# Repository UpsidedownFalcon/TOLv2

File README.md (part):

# TOLv2: Wearable IMU Logger for Synchronised Multi-Person Motion Capture 

## Contents

- [Introduction](#introduction)
- [Rationale](#rationale)
- [System overview](#system-overview)
  - [Level 1: system context](#level-1-system-context)
  - [Level 2: modules](#level-2-modules)
- [System breakdown](#system-breakdown)
  - [USBC: connector and protection](#usbc-connector-and-protection)
  - [BMS: charger, fuel gauge and cell](#bms-charger-fuel-gauge-and-cell)
  - [SNS: sensors and main rail](#sns-sensors-and-main-rail)
  - [MCU: SoC, clocks and radio](#mcu-soc-clocks-and-radio)
  - [SD: card and card rail](#sd-card-and-card-rail)
  - [UI: button, LED and debug](#ui-button-led-and-debug)
  - [PCB](#pcb)
- [JLCPCB ordering](#jlcpcb-ordering)
- [Firmware rules](#firmware-rules)
  - [F1: charger](#f1-charger)
  - [F2: storage](#f2-storage)
  - [F3: sensors](#f3-sensors)
  - [F4: clock](#f4-clock)
  - [F5: card](#f5-card)
  - [F6: GPIO and buses](#f6-gpio-and-buses)
  - [F7: timing and sleep](#f7-timing-and-sleep)
  - [F8: recovery](#f8-recovery)
  - [Rails](#rails)
  - [IMU](#imu)

## Introduction

TOL v2 is an open-hardware inertial logger that a person wears. The logger records acceleration, angular rate and magnetic field. A maximum of 32 devices record on one time reference.

- **Size:** 35.4 mm × 21.4 mm × 9.9 mm with battery and enclosure.
- **IMU (inertial measurement unit):** 6-axis ICM-45686, anti-aliased output, 6.4 kHz maximum.
- **Magnetometer:** 3-axis MMC5983MA, output 1 kHz maximum.
- **Cell:** 150 mAh LiPo. Approximately 9 days of continuous record at 100 Hz (0.64 mA).
- **Standby:** approximately 6 months at 32 µA, with wake on motion.
- **Card:** removable microSD card, 8 GB minimum.
- **USB-C:** cell charge and full-speed data transfer (12 Mbit/s).
- **Radio:** Bluetooth Low Energy (BLE) with a long-range mode and a 2 Mbit/s mode.
- **Sync:** BLE beacons give the time reference. The target error between devices is 1 ms.
- **Clock:** one temperature-compensated crystal oscillator (TCXO) for the system on chip (SoC) and the IMU. Hardware timestamps for events.
- **Charge control:** programmable charger and fuel gauge.

## Rationale

TOL v2 is designed as a successor to the Tiny Open Logger (TOL v1): 

| Gap in earlier work | Source | TOL v2 response |
|---|---|---|
| A timestamp is a sample count multiplied by a nominal interval. | TOL v1 | The interrupt lines of the sensors connect to a capture timer. A TCXO is the clock source of the real-time counter. |
| The clock rates of 2 devices are different by 40 to 67 ppm. The offset is 336 ms maximum after 2 h. | TOL v1 | Each device has a TCXO with a tolerance of ±1.9 ppm at 0 to 50 °C. |
| There is no sync between devices. Sync with magnet pulses has an error of 7 to 40 ms and a range of 11 cm. | TOL v1 | BLE beacons give one time reference to all devices. The target error is 1 ms. |
| A device that streams data has sync. But this device uses 350 mA and needs Wi-Fi and a server. | HARNode (Lepold et al., 2025) | Each device records to its card. The current calculation has the receiver on for 2 ms each second. |
| The download uses flash memory at 1 MHz, CSV text and one Wi-Fi access point for each device. | TOL v1 | The card is removable. USB transfers the files at full speed. USB hubs connect a group of devices to one host PC. |
| There is no sleep mode, no fuel gauge and no measured current. The SoC uses 17 to 28 mA. | TOL v1 | Calculated current: 0.58 mA in normal record mode, 32 µA in standby. The board has a fuel gauge and a programmable charger. |
| Rules for home-made boards limit the design. Manual assembly of LGA parts is not a task for a non-expert. | TOL v1 | An assembly service makes the board. All fitted parts are in the JLCPCB parts library. |
| The button shares a boot pin of the SoC. | TOL v1 | The button connects to a GPIO pin with no boot function. |
| Sessions have 6 to 20 persons and last approximately 2 h. Download was one device at a time. Children touch the devices. Sweat goes into the devices. | Ward et al., 2018; Sun et al., 2026 | A maximum of 32 devices. Charge and download through USB hubs. One button, for use below a membrane. |

## System overview

### System context

```mermaid
flowchart LR
    wearer("Wearer")
    researcher("Researcher")
    beacon["Beacon source<br/>BLE time reference"]
    host["Host PC and USB hubs<br/>5 V supply, file download"]
    probe["Debug probe<br/>SWD"]
    tol["TOL v2 device<br/>records motion with hardware timestamps"]

    wearer -->|"motion, magnetic field"| tol
    researcher -->|"button"| tol
    tol -->|"LED: identity, state, charge"| researcher
    beacon -->|"BLE beacons"| tol
    host ==>|"USB-C: 5 V"| tol
    tol -->|"USB: files"| host
    probe -->|"program, debug"| tol
```

- The researcher starts and stops a session with the button.
- The LED shows the device identity, the device state and the state of charge.
- The beacon source sends a BLE beacon at intervals of 60 s maximum. This repository does not contain a beacon source.

### Modules

```mermaid
flowchart TB
    subgraph board["TOL v2 device"]
        direction TB
        USBC["USBC<br/>J1 receptacle, D1 ESD"]
        BMS["BMS<br/>U2 charger, U3 fuel gauge, BT1 cell"]
        SNS["SNS<br/>U7 regulator, U5 IMU, U6 magnetometer"]
        MCU["MCU<br/>U1 SoC, Y1 TCXO, X1 crystal, ANT1"]
        SD["SD<br/>U4 regulator, J2 microSD socket"]
        UI["UI<br/>SW1 button, D2 LED, J3 debug pads"]
    end

    USBC ==>|"VBUS"| BMS
    USBC ==>|"VBUS"| MCU
    BMS ==>|"SYS"| SNS
    BMS ==>|"SYS"| SD
    BMS ==>|"SYS"| UI
    SNS ==>|"VDD 3.0 V"| MCU
    SNS ==>|"VDD 3.0 V"| UI

    USBC ---|"USB, 12 Mbit/s"| MCU
    SNS ---|"SPIM2 4 MHz<br/>TWIM1 100 kHz<br/>IMU_INT, MAG_INT<br/>CLK32K_IMU 32.768 kHz"| MCU
    MCU ---|"SPIM3 16 MHz<br/>SD_EN, SD_DET"| SD
    BMS ---|"TWIM0 100 kHz<br/>CHG_INT, FG_ALRT"| MCU
    MCU ---|"LED_DIN, BTN, SWD"| UI
    MCU -.-> SNS
```

External connections: host PC to USBC, beacon source to MCU, wearer to SNS, researcher and debug probe to UI.

| Module | Input | Process | Output |
|---|---|---|---|
| USBC (USB-C connector) | 5 V and USB data from the cable; electrostatic discharge | Identifies the device as a power sink. Clamps electrostatic discharges. | `VBUS`; USB data pair |
| BMS (battery management) | `VBUS`; settings on TWIM0 | Selects the power source. Charges the cell. Measures the state of charge. | `SYS`; `CHG_INT`; `FG_ALRT`; state-of-charge data on TWIM0 |
| SNS (sensors) | `SYS`; motion; magnetic field; `CLK32K_IMU`; commands on SPIM2 and TWIM1 | Regulates `SYS` to 3.0 V. Measures acceleration, angular rate and magnetic field. | `VDD`; samples on SPIM2 and TWIM1; `IMU_INT`; `MAG_INT` |
| MCU (microcontroller) | `VDD`; `VBUS`; samples; `IMU_INT`; `MAG_INT`; `BTN`; `SD_DET`; `CHG_INT`; `FG_ALRT`; state-of-charge data; beacons; USB data | Gives timestamps to events. Holds samples in a buffer. Writes files. Operates BLE and USB. | Card data on SPIM3; `SD_EN`; `LED_DIN`; `CLK32K_IMU`; commands on SPIM2 and TWIM1; settings on TWIM0; BLE packets; USB data |
| SD (card) | `SYS`; `SD_EN`; card data on SPIM3 | Switches the card rail. Stores files. | `SD_DET`; card data on SPIM3 |
| UI (user interface) | `SYS`; `VDD`; button press; `LED_DIN`; SWD signals from the debug probe | Sets `BTN` high during a press. Shows the device state. Connects the debug probe to the SoC. | `BTN`; light; SWD signals to the SoC |

**Power**

```mermaid
flowchart LR
    J1["J1 USB-C"] ==>|"VBUS 5 V"| U2["U2 charger<br/>power path"]
    BT1["BT1 cell<br/>150 mAh"] ==>|"BAT"| U2
    BT1 ---|"BAT"| U3["U3 fuel gauge"]
    U2 ==>|"SYS"| U7["U7 regulator<br/>always on"]
    U2 ==>|"SYS"| U4["U4 regulator<br/>switched by SD_EN"]
    U2 ==>|"SYS"| D2["D2 LED"]
    U7 ==>|"VDD 3.0 V"| loads["U1 SoC, U5 IMU,<br/>U6 magnetometer, Y1 TCXO"]
    U4 ==>|"3V0_SD 3.0 V"| J2["J2 microSD socket"]
    J1 ==>|"VBUS through R5"| usb["U1 USB supply pin"]
```

- U2 supplies `SYS` from `VBUS` when `VBUS` is present. If not, U2 supplies `SYS` from the cell.
- U7 supplies the main rail `VDD` (3.0 V) at all times.
- U4 supplies the card rail `3V0_SD` (3.0 V) only while `SD_EN` is high.

**Data**

- The IMU and the card each have an SPI master. A card write does not stop a sensor read.
- The charger and the fuel gauge share one I2C bus. The magnetometer has a second I2C bus.

**Timing**

```mermaid
flowchart LR
    Y1["Y1 TCXO<br/>32.768 kHz"] -.->|"R1"| RTC["RTC<br/>30.5 µs periods"]
    Y1 -.->|"R2"| U5["U5 IMU<br/>sample clock"]
    X1["X1 crystal<br/>32 MHz"] -.-> TIMER["Capture timer<br/>62.5 ns ticks"]
    RTC -->|"event: start"| TIMER
    U5 -->|"IMU_INT: capture"| TIMER
    U6["U6 magnetometer"] -->|"MAG_INT: capture"| TIMER
    RADIO["RADIO<br/>beacon address"] -->|"capture"| TIMER
    RTC --> TS["Timestamp =<br/>RTC count + timer ticks"]
    TIMER --> TS
```

- Y1 is the clock source of the real-time counter (RTC) of the SoC and of the IMU.
- An RTC event starts the capture timer. A sensor edge or a beacon captures the timer value.
- The capture timer operates only in a capture interval. The current calculation uses one interval of 2 ms each second.
- Each device calculates its offset and rate from the beacons.

**Modes**

| Mode | Calculated current | Wake source |
|---|---|---|
| Normal record mode | 0.58 mA | |
| Standby | 32 µA | Motion |
| Off | 15.1 µA | Button |
| Device storage | 3.5 µA | |

- Normal record mode: IMU setting 100 Hz, magnetometer 25 Hz.
- High-rate record mode: IMU setting 400 Hz, magnetometer 100 Hz.
- Records use 16-bit samples.
- In off mode the SoC is in System OFF. A button press starts the SoC.

## System breakdown
### USBC: connector and protection

Sheet: [electronics/USBC.kicad_sch](electronics/USBC.kicad_sch)

| Part | Input | Process | Output |
|---|---|---|---|
| J1 USB-C receptacle, R3, R4 | 5 V and USB data from a USB host or charger | Connects the cable to the board. R3 and R4 (5.1 kΩ) identify the device as a power sink. | `VBUS` (5 V); `USB_D+`; `USB_D-` |
| D1 ESD array (AOZ8904CIL) | Electrostatic discharge on `USB_D+`, `USB_D-` or `VBUS` | Clamps the line voltage. | Clamped voltage on the line |

- USB 2.0 only. The CC lines connect only to R3 and R4. The device can use default USB power only.
- The USB data pair connects directly to the SoC. The speed is 12 Mbit/s (full speed).
- The working voltage of D1 is 5.5 V. D1 does not protect the USB supply pin of the SoC.
- The capacitance on `VBUS` is 9.4 µF nominal and 10.3 µF at +10 % tolerance. The USB-C limit for a sink is 10 µF.

### BMS: charger, fuel gauge and cell

Sheet: [electronics/BMS.kicad_sch](electronics/BMS.kicad_sch)

| Part | Input | Process | Output |
|---|---|---|---|
| U2 charger (BQ25180, I2C address 0x6A) | `VBUS`; `BAT`; temperature signal from RT1; settings on TWIM0 | Supplies `SYS` from `VBUS` or from the cell. Charges the cell at the set current and voltage. | `SYS`; charge current; `CHG_INT` |
| U3 fuel gauge (MAX17048, I2C address 0x36) | Cell voltage on `BAT` | Calculates the state of charge. | State-of-charge data on TWIM0; `FG_ALRT` |
| RT1 thermistor (10 kΩ NTC) | Board temperature near U2 | Changes its resistance with temperature. | Temperature signal to U2 |
| BT1 pads for the cell pack | Charge current from U2 | The cell pack stores the energy. | `BAT` |

- A cell pack is a 150 mAh LiPo cell with a protection circuit. The assembler does not fit the cell pack.
- Firmware writes the charge settings for this cell. See [F1](#f1-charger).
- Only the fuel gauge measures the cell voltage. See [Rails](#rails).
- The board has no protection circuit and no reverse-polarity protection.
- Pad 1 of BT1 is positive. Examine the polarity before you solder the cell pack.
- Cell limits: charge at 150 mA maximum, at 0 to 45 °C. Discharge at 300 mA maximum.

### SNS: sensors and main rail

Sheet: [electronics/SNS.kicad_sch](electronics/SNS.kicad_sch)

| Part | Input | Process | Output |
|---|---|---|---|
| U7 regulator (TPS7A0230) | `SYS` | Regulates `SYS` to 3.0 V at all times. | `VDD` for the SoC, the sensors, the TCXO and the pull-up resistors |
| U5 IMU (ICM-45686) | `VDD`; motion; `CLK32K_IMU`; commands on SPIM2 | Measures acceleration and angular rate on 3 axes each. Holds 8 kB maximum in its buffer. | Samples on SPIM2; `IMU_INT` (data ready or buffer level) |
| U6 magnetometer (MMC5983MA, I2C address 0x30) | `VDD`; magnetic field; commands on TWIM1 | Measures the field on 3 axes with 18 bits. | Samples on TWIM1; `MAG_INT` (measurement complete) |

- The enable pin of U7 connects to `SYS`. Firmware cannot set `VDD` to off. The sensors sleep by command ([F3](#f3-sensors)).
- With the clock from Y1, the IMU rate is the set rate × 1.024. A setting of 100 Hz gives 102.4 Hz.
- TDK application note AN-000478 gives this ratio for low-noise mode. The design uses the same ratio for low-power mode.
- `VDD` stays at 3.0 V until `SYS` decreases to approximately 3.3 V. Below this voltage, `VDD` decreases with `SYS`.
- Minimum supply voltage: magnetometer 2.8 V, IMU 1.71 V, SoC 1.7 V.
- U7 is stable with 0.5 to 22 µF. `VDD` has 13.1 to 20.8 µF effective (calculated).

### MCU: SoC, clocks and radio

Sheet: [electronics/MCU.kicad_sch](electronics/MCU.kicad_sch)

| Part | Input | Process | Output |
|---|---|---|---|
| U1 SoC (nRF52840) | `VDD`; `VBUS` through R5; `CLK32_MCU`; samples; `IMU_INT`; `MAG_INT`; `BTN`; beacons; USB data | Gives timestamps to events. Holds samples in a buffer. Writes files to the card. Operates BLE and USB. | Card data on SPIM3; `SD_EN`; `LED_DIN`; sensor commands; charger settings; BLE packets; USB data |
| Y1 TCXO (TG-3541CE), R24, C47 | `VDD` through the filter R24 and C47 | Makes a 32.768 kHz clock with temperature compensation. | `CLK32_MCU` through R1; `CLK32K_IMU` through R2 |
| X1 crystal (32 MHz), C1, C2 | Drive from U1 | Sets the frequency of the high-frequency clock. | Clock for the radio, USB and the capture timer |
| ANT1 chip antenna, C3, L1, C4, L5, L6 | 2.4 GHz signal from U1; radio waves | Connects U1 to the antenna through the matching network. Transmits and receives. | Radio waves; 2.4 GHz signal to U1 |

SoC pin map. High is `VDD` (3.0 V). Low is ground. TWIM, SPIM and I2S are peripherals of the nRF52840.

| Pin | Net | Direction | Function | Notes |
|---|---|---|---|---|
| `P0.00` | `CLK32_MCU` | In | XL1 | 32.768 kHz from Y1 through R1 |
| `P0.04` | `BTN` | In | GPIO, wake | High = press. Internal pull-down |
| `P0.05` | `MAG_INT` | In | Timer capture | High = measurement complete |
| `P0.06` | `IMU_MISO` | In | SPIM2 MISO | |
| `P0.07` | `IMU_INT` | In | Timer capture | Data ready or buffer level |
| `P0.08` | `IMU_CS` | Out | GPIO | Low = IMU selected |
| `P0.11` | `BMS_SCL` | Out | TWIM0 SCL | R6, 10 kΩ to `VDD` |
| `P0.12` | `BMS_SDA` | In/out | TWIM0 SDA | R7, 10 kΩ to `VDD` |
| `P0.13` | `LED_DIN` | Out | I2S data out | R22 pull-down. Idle low |
| `P0.14` | `SD_EN` | Out | GPIO | High = card rail on. R20 pull-down |
| `P0.15` | `CHG_INT` | In | GPIO | Low pulse = charger event. Internal pull-up |
| `P0.16` | `SD_DET` | In | GPIO | Low = no card. Internal pull-up only during a read |
| `P0.17` | `SD_CS` | Out | SPIM3 CSN | Low = card selected |
| `P0.18` | `NRESET` | In | Reset | From J3. Only after UICR PSELRESET = 18 |
| `P0.19` | `SD_SCK` | Out | SPIM3 SCK | R21 pull-down |
| `P0.20` | `MAG_SCL` | Out | TWIM1 SCL | R9, 10 kΩ to `VDD` |
| `P0.21` | `SD_MOSI` | Out | SPIM3 MOSI | To the card CMD pin |
| `P0.22` | `MAG_SDA` | In/out | TWIM1 SDA | R19, 10 kΩ to `VDD` |
| `P0.23` | `SD_MISO` | In | SPIM3 MISO | From the card DAT0 pin |
| `P0.25` | `FG_ALRT` | In | GPIO | Low = alert. Internal pull-up |
| `P0.26` | `IMU_SCK` | Out | SPIM2 SCK | |
| `P0.27` | `IMU_MOSI` | Out | SPIM2 MOSI | |
| `P1.00` | `SWO` | Out | Trace | To J3. Optional |

- GPIO pins that are not in the table have no connection. The I2S block uses `P0.24` and `P1.08` as clock outputs ([F6](#f6-gpio-and-buses)).
- The SoC operates in normal voltage mode. Its 2 supply inputs connect to `VDD`. See [Rails](#rails).
- Y1 tolerance: ±1.9 ppm at 0 to 50 °C. Y1 gives a valid clock 3 s maximum after power-on.
- Y1 needs its supply at 0 V for more than 10 s before a new power-on.
- With no beacon for 10 min, the time difference between 2 devices increases to 2.3 ms maximum (calculated).
- The 2.3 ms figure includes only the ±1.9 ppm tolerance of Y1. With solder shift, ageing and supply tolerance, the figure is 10.7 ms.
- The target timestamp error is 5 µs.
- C44 and C45 are not fitted. They are positions for antenna tuning parts. The matching network is not tuned for this board.
- TP4 is a bare test pad on the output of Y1.
- C9 (820 pF) is necessary for this SoC variant, NRF52840-QIAA-R.
- The debug port is not locked on this SoC variant.

### SD: card and card rail

Sheet: [electronics/SD.kicad_sch](electronics/SD.kicad_sch)

| Part | Input | Process | Output |
|---|---|---|---|
| U4 regulator (TPS7A0230) | `SYS`; `SD_EN` | Supplies 3.0 V while `SD_EN` is high. Discharges the card rail when off. | `3V0_SD` |
| J2 microSD socket (TF-110) and card | `3V0_SD`; card data on SPIM3 | Operates in SPI mode. Stores the files. | Card data on SPIM3; `SD_DET` (low = no card) |
| R12 to R16, R20, R21 | SoC pins that float during a reset | R12 to R16 pull the card lines up to `3V0_SD`. R20 holds `SD_EN` low. R21 holds `SD_SCK` low. | Defined levels on the card lines |

- The assembler does not fit a card.
- Data rate: 1.9 kB/s (21 MB in 3 h) in normal record mode, 7.8 kB/s (84 MB in 3 h) in high-rate record mode.
- The card rail is on only during a buffer write: approximately each 67 s in normal record mode.
- R12 to R16 connect to `3V0_SD`. As a result, the resistors cannot supply a card that has no power.

### UI: button, LED and debug

Sheet: [electronics/UI.kicad_sch](electronics/UI.kicad_sch)

| Part | Input | Process | Output |
|---|---|---|---|
| SW1 button | A press; `VDD` | Connects `VDD` to `BTN` during a press. | `BTN` (high = press) |
| D2 RGB LED (WS2812B) | `SYS`; `LED_DIN` at 800 kbit/s | Decodes the colour data. | Light: device identity, device state, state of charge |
| J3 debug pads (Tag-Connect TC2030) | SWD signals from the debug probe | Connects the debug probe to the SoC. | `SWDIO`; `SWCLK`; `NRESET`; `SWO` |

- J3 has 6 bare pads: `VDD`, `SWDIO`, `NRESET`, `SWCLK`, GND, `SWO`.
- TP1, TP2, TP3 and TP5 are bare test pads: `BAT`, `SYS`, `VDD`, GND.
- `SYS` supplies the LED. The LED data level comes from `VDD`. This level limits `SYS` to 4.4 V. See [F1](#f1-charger).
- The sensor interrupt lines have no test pads.

### PCB

Board: [electronics/TOLv2.kicad_pcb](electronics/TOLv2.kicad_pcb). Custom rules: [electronics/TOLv2.kicad_dru](electronics/TOLv2.kicad_dru).

- Size: 26.5 mm × 17.78 mm. Copper layers: 6. Finish: ENIG.
- Stack-up: JLC06081H-2116. Thickness: 0.83 mm ± 0.10 mm.
- Footprints: 81. 70 are on the top side and 11 are on the bottom side. The assembler fits 72.
- Not fitted: BT1, J3, TP1 to TP5, C44, C45.
- Vias: 178 through vias, all filled and capped. 99 are in a pad. 124 have a 0.15 mm hole.
- Minimum track and gap: 0.10 mm.
- Target impedance (calculated): 50 Ω for the antenna feed, 90 Ω for the USB data pair.
- KiCad 10.0.8 checks: DRC gives 0 violations. ERC gives 0 errors and 3 label warnings.

| Layer | Use |
|---|---|
| Top | Most parts, antenna feed, crystal, TCXO |
| Inner 1 | Ground plane |
| Inner 2 | Signals |
| Inner 3 | `VDD` pour; `VBUS`, `BAT` and `SYS` tracks |
| Inner 4 | Ground plane |
| Bottom | microSD socket, charger, USB data pair, card lines, debug pads |

## JLCPCB ordering

The production files are in [electronics/production/](electronics/production/).

| File | Content |
|---|---|
| `electronics/production/TOLv2.zip` | Gerber and drill files |
| `electronics/production/bom.csv` | Bill of materials (BOM): 37 lines, each with an LCSC part number |
| `electronics/production/positions.csv` | Placement file (CPL): 72 parts on 2 sides |

1. Go to [jlcpcb.com](https://jlcpcb.com). Click **Instant Quote**.
2. Upload `electronics/production/TOLv2.zip`. The page reads the board size and the number of layers.
3. Set the PCB options:

   | Option | Value | Reason |
   |---|---|---|
   | Base Material | FR-4 | |
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
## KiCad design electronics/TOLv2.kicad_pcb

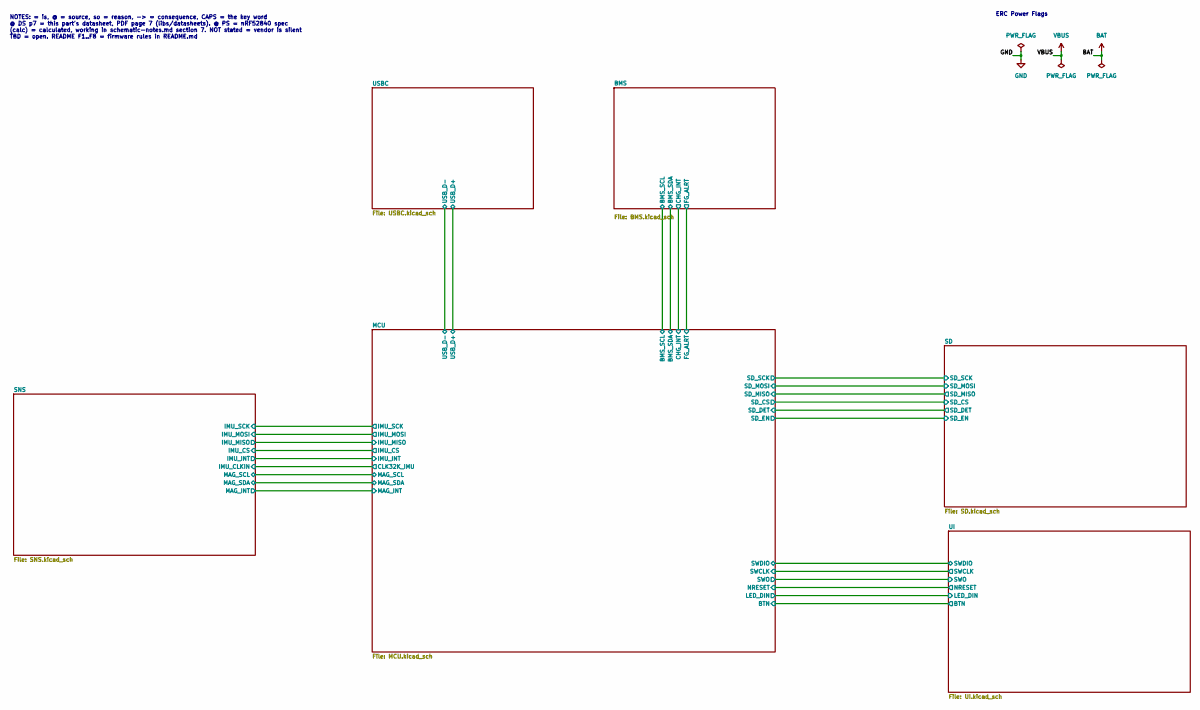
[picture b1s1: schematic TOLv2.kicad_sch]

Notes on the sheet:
ERC Power Flags
NOTES: = is, @ = source, so = reason, -> = consequence, CAPS = the key word @ DS p7 = this part's datasheet, PDF page 7 (libs/datasheets). @ PS = nRF52840 spec (calc) = calculated, working in schematic-notes.md section 7. NOT stated = vendor is silent TBD = open. README F1..F8 = firmware rules in R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

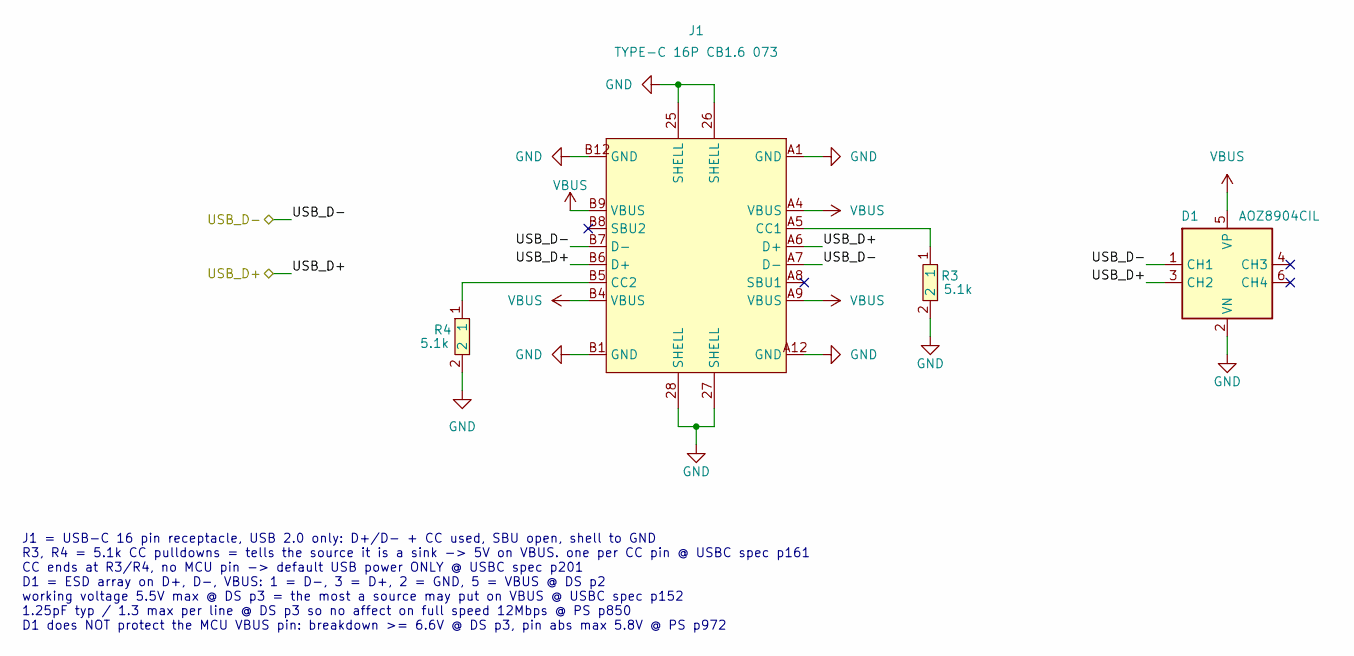
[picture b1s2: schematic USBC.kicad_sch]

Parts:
D1: AOZ8904CIL; ESD_AOZ8904CIL; MPN AOZ8904CIL; LCSC Part # C2649893
J1: TYPE-C 16P CB1.6 073; CONN_USBC16_TYPE-C-16P-CB1p6-073; MPN TYPE-C 16P CB1.6 073; LCSC Part # C2906290
R3, R4: 5.1k; RES_5k1_0402_0402WGF5101TCE; Tolerance +-1%; MPN 0402WGF5101TCE; LCSC Part # C25905

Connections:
/USBC/USB_D+: D1.3 (CH2), J1.A6 (D+), J1.B6 (D+); also elsewhere on the board
/USBC/USB_D-: D1.1 (CH1), J1.A7 (D-), J1.B7 (D-); also elsewhere on the board
GND: D1.2 (VN), J1.25 (SHELL), J1.26 (SHELL), J1.27 (SHELL), J1.28 (SHELL), J1.A1 (GND), J1.A12 (GND), J1.B1 (GND), J1.B12 (GND), R3.2, R4.2; also elsewhere on the board
unnamed: J1.A5 (CC1), R3.1
unnamed: J1.B5 (CC2), R4.1
VBUS: D1.5 (VP), J1.A4 (VBUS), J1.A9 (VBUS), J1.B4 (VBUS), J1.B9 (VBUS); also elsewhere on the board

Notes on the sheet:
J1 = USB-C 16 pin receptacle, USB 2.0 only: D+/D- + CC used, SBU open, shell to GND R3, R4 = 5.1k CC pulldowns = tells the source it is a sink -> 5V on VBUS. one per CC pin @ USBC spec p161 CC ends at R3/R4, no MCU pin -> default USB power ONLY @ USBC spec p201 D1 = ESD array on D+, D-, VBUS: 1 = D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

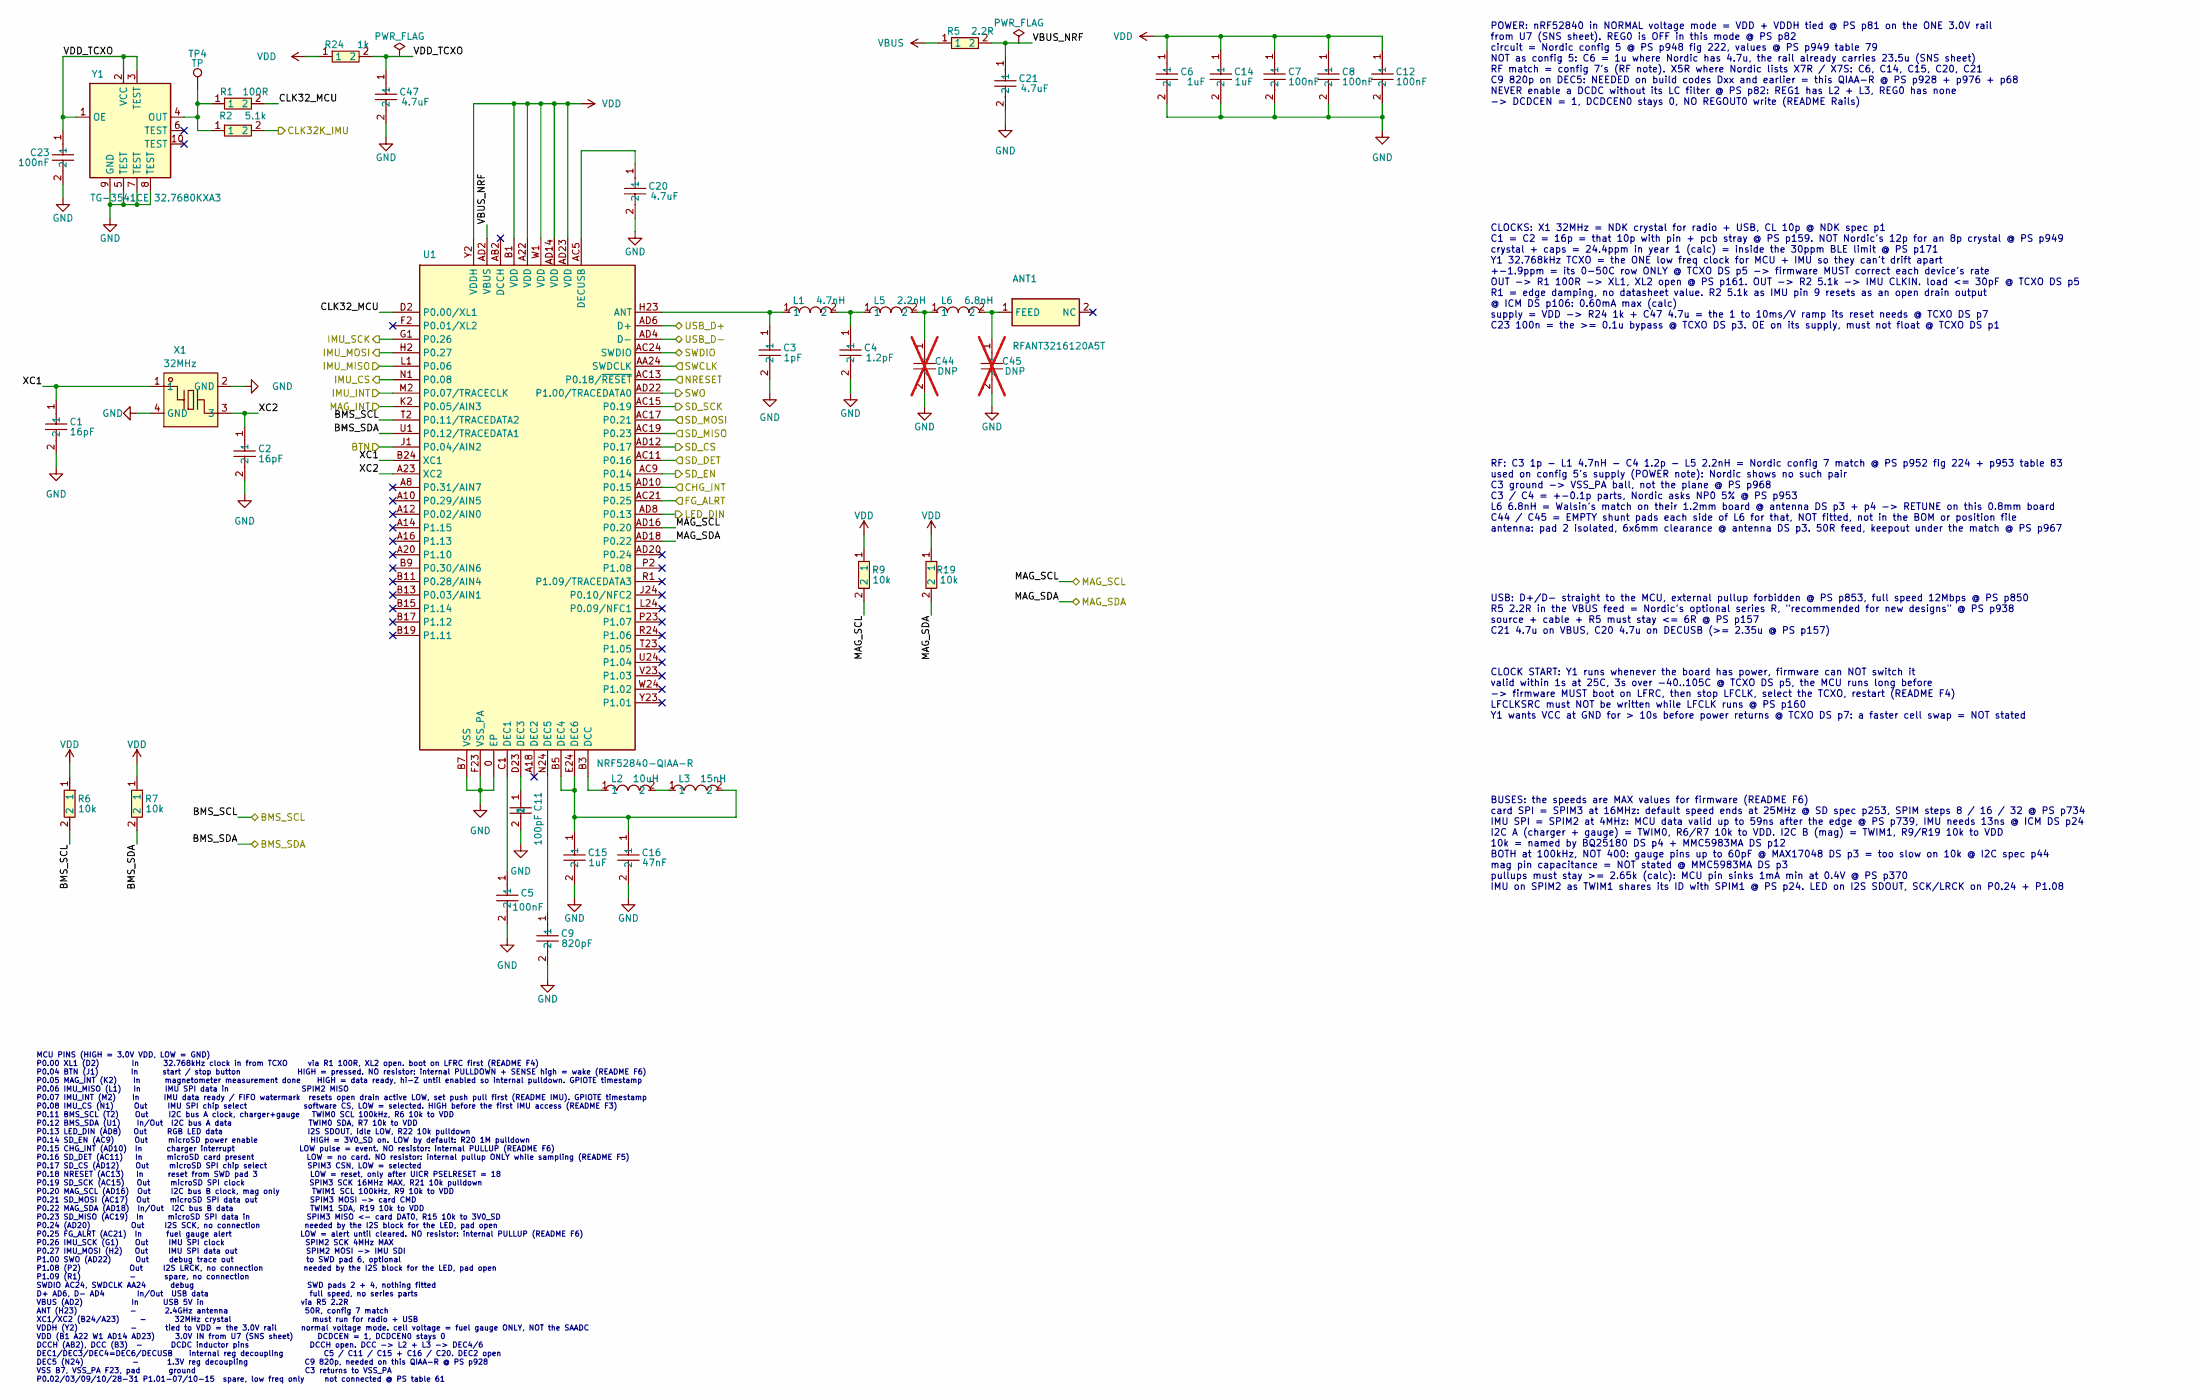
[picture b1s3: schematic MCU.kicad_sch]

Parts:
ANT1: RFANT3216120A5T; ANT_RFANT3216120A5T; MPN RFANT3216120A5T; LCSC Part # C127629
C1, C2: 16pF; CAP_16pF_50V_NP0_0402_CC0402GRNPO9BN160; Tolerance +-2%; Voltage 50V; MPN CC0402GRNPO9BN160; LCSC Part # C513591
C3: 1pF; CAP_1pF_50V_NP0_0402_CC0402BRNPO9BN1R0; Tolerance +-0.1pF; Voltage 50V; MPN CC0402BRNPO9BN1R0; LCSC Part # C309455
C4: 1.2pF; CAP_1p2_50V_C0G_0402_0402CG1R2B500NT; Tolerance +-0.1pF; Voltage 50V; MPN 0402CG1R2B500NT; LCSC Part # C575437
C5, C7, C8, C12, C23: 100nF; CAP_100nF_16V_X7R_0402_CL05B104KO5NNNC; Tolerance +-10%; Voltage 16V; MPN CL05B104KO5NNNC; LCSC Part # C1525
C6, C14, C15: 1uF; CAP_1uF_25V_X5R_0402_CL05A105KA5NQNC; Tolerance +-10%; Voltage 25V; MPN CL05A105KA5NQNC; LCSC Part # C52923
C9: 820pF; CAP_820pF_50V_C0G_0402_0402CG821J500NT; Tolerance +-5%; Voltage 50V; MPN 0402CG821J500NT; LCSC Part # C913875
C11: 100pF; CAP_100pF_50V_C0G_0402_0402CG101J500NT; Tolerance +-5%; Voltage 50V; MPN 0402CG101J500NT; LCSC Part # C1546
C16: 47nF; CAP_47nF_25V_X7R_0402_TCC0402X7R473K250AT; Tolerance +-10%; Voltage 25V; MPN TCC0402X7R473K250AT; LCSC Part # C466239
C20, C21, C47: 4.7uF; CAP_4u7_16V_X5R_0603_CL10A475KO8NNNC; Tolerance +-10%; Voltage 16V; MPN CL10A475KO8NNNC; LCSC Part # C19666
C44, C45: DNP; CAP_DNP_0402; not fitted
L1: 4.7nH; IND_4n7_0402_VHF100505HQ4N7BT; Tolerance +-0.1nH; MPN VHF100505HQ4N7BT; LCSC Part # C3032786
L2: 10uH; IND_10uH_0603_MYH1608N100MT; Tolerance +-20%; MPN MYH1608N100MT; LCSC Part # C55079856
L3: 15nH; IND_15nH_0402_VHF100505H15NKT; Tolerance +-10%; MPN VHF100505H15NKT; LCSC Part # C381880
L5: 2.2nH; IND_2n2_0402_TCGL1005B2N2BAT; Tolerance +-0.1nH; MPN TCGL1005B2N2BAT; LCSC Part # C52109817
L6: 6.8nH; IND_6n8_0402_TCGL1005B6N8JAT; Tolerance +-5%; MPN TCGL1005B6N8JAT; LCSC Part # C52109831
R1: 100R; RES_100R_0402_0402WGF1000TCE; Tolerance +-1%; MPN 0402WGF1000TCE; LCSC Part # C25076
R2: 5.1k; RES_5k1_0402_0402WGF5101TCE; Tolerance +-1%; MPN 0402WGF5101TCE; LCSC Part # C25905
R5: 2.2R; RES_2R2_0402_SCR0402F2R2; Tolerance +-1%; MPN SCR0402F2R2; LCSC Part # C3015708
R6, R7, R9, R19: 10k; RES_10k_0402_0402WGF1002TCE; Tolerance +-1%; MPN 0402WGF1002TCE; LCSC Part # C25744
R24: 1k; RES_1k_0402_0402WGF1001TCE; Tolerance +-1%; MPN 0402WGF1001TCE; LCSC Part # C11702
TP4: TP; TP_0p6mm
U1: NRF52840-QIAA-R; MCU_NRF52840-QIAA-R; MPN NRF52840-QIAA-R; LCSC Part # C190794
X1: 32MHz; XTAL_32MHz_2016_NX2016SA-32M-EXS00A-CS06465; Tolerance +-10ppm; MPN NX2016SA-32M-EXS00A-CS06465; LCSC Part # C1986260
Y1: TG-3541CE 32.7680KXA3; TCXO_32k768_TG-3541CE; MPN TG-3541CE 32.7680KXA3; LCSC Part # C1987384

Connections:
/BMS/BMS_SCL: R6.2, U1.T2 (P0.11/TRACEDATA2); also elsewhere on the board
/BMS/BMS_SDA: R7.2, U1.U1 (P0.12/TRACEDATA1); also elsewhere on the board
/BMS/CHG_INT: U1.AD10 (P0.15); also elsewhere on the board
/BMS/FG_ALRT: U1.AC21 (P0.25); also elsewhere on the board
/MCU/BTN: U1.J1 (P0.04/AIN2); also elsewhere on the board
/MCU/CLK32K_IMU: R2.2; also elsewhere on the board
/MCU/CLK32_MCU: R1.2, U1.D2 (P0.00/XL1)
/MCU/IMU_CS: U1.N1 (P0.08); also elsewhere on the board
/MCU/IMU_INT: U1.M2 (P0.07/TRACECLK); also elsewhere on the board
/MCU/IMU_MISO: U1.L1 (P0.06); also elsewhere on the board
/MCU/IMU_MOSI: U1.H2 (P0.27); also elsewhere on the board
/MCU/IMU_SCK: U1.G1 (P0.26); also elsewhere on the board
/MCU/LED_DIN: U1.AD8 (P0.13); also elsewhere on the board
/MCU/MAG_INT: U1.K2 (P0.05/AIN3); also elsewhere on the board
/MCU/MAG_SCL: R9.2, U1.AD16 (P0.20); also elsewhere on the board
/MCU/MAG_SDA: R19.2, U1.AD18 (P0.22); also elsewhere on the board
/MCU/NRESET: U1.AC13 (P0.18/~RESET); also elsewhere on the board
/MCU/SD_CS: U1.AD12 (P0.17); also elsewhere on the board
/MCU/SD_DET: U1.AC11 (P0.16); also elsewhere on the board
/MCU/SD_EN: U1.AC9 (P0.14); also elsewhere on the board
/MCU/SD_MISO: U1.AC19 (P0.23); also elsewhere on the board
/MCU/SD_MOSI: U1.AC17 (P0.21); also elsewhere on the board
/MCU/SD_SCK: U1.AC15 (P0.19); also elsewhere on the board
/MCU/SWCLK: U1.AA24 (SWDCLK); also elsewhere on the board
/MCU/SWDIO: U1.AC24 (SWDIO); also elsewhere on the board
/MCU/SWO: U1.AD22 (P1.00/TRACEDATA0); also elsewhere on the board
/MCU/VBUS_NRF: C21.1, R5.2, U1.AD2 (VBUS)
/MCU/VDD_TCXO: C23.1, C47.1, R24.2, Y1.1 (OE), Y1.2 (VCC), Y1.3 (TEST)
/MCU/XC1: C1.1, U1.B24 (XC1), X1.1
/MCU/XC2: C2.1, U1.A23 (XC2), X1.3
/USBC/USB_D+: U1.AD6 (D+); also elsewhere on the board
/USBC/USB_D-: U1.AD4 (D-); also elsewhere on the board
GND: C1.2, C2.2, C3.2, C4.2, C5.2, C6.2, C7.2, C8.2, C9.2, C11.2, C12.2, C14.2, C15.2, C16.2, C20.2, C21.2, C23.2, C44.2, C45.2, C47.2, U1.0 (EP), U1.B7 (VSS), U1.F23 (VSS_PA), X1.2 (GND), X1.4 (GND), Y1.5 (TEST), Y1.7 (TEST), Y1.8 (TEST), Y1.9 (GND); also elsewhere on the board
unnamed: ANT1.1 (FEED_1), C45.1, L6.2
unnamed: C4.1, L1.2, L5.1
unnamed: C44.1, L5.2, L6.1
unnamed: L2.2, L3.1
unnamed: C3.1, L1.1, U1.H23 (ANT)
unnamed: L2.1, U1.B3 (DCC)
unnamed: C5.1, U1.C1 (DEC1)
unnamed: C11.1, U1.D23 (DEC3)
unnamed: C15.1, C16.1, L3.2, U1.B5 (DEC4), U1.E24 (DEC6)
unnamed: C9.1, U1.N24 (DEC5)
unnamed: C20.1, U1.AC5 (DECUSB)
unnamed: R1.1, R2.1, TP4.1 (1_1), Y1.4 (OUT)
VBUS: R5.1; also elsewhere on the board
VDD: C6.1, C7.1, C8.1, C12.1, C14.1, R6.1, R7.1, R9.1, R19.1, R24.1, U1.A22 (VDD), U1.AD14 (VDD), U1.AD23 (VDD), U1.B1 (VDD), U1.W1 (VDD), U1.Y2 (VDDH); also elsewhere on the board

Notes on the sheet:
POWER: nRF52840 in NORMAL voltage mode = VDD + VDDH tied @ PS p81 on the ONE 3.0V rail from U7 (SNS sheet). REG0 is OFF in this mode @ PS p82 circuit = Nordic config 5 @ PS p948 fig 222, values @ PS p949 table 79 NOT as config 5: C6 = 1u where Nordic has 4.7u, the rail already carries 23.5u (SNS sh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
CLOCKS: X1 32MHz = NDK crystal for radio + USB, CL 10p @ NDK spec p1 C1 = C2 = 16p = that 10p with pin + pcb stray @ PS p159. NOT Nordic's 12p for an 8p crystal @ PS p949 crystal + caps = 24.4ppm in year 1 (calc) = inside the 30ppm BLE limit @ PS p171 Y1 32.768kHz TCXO = the ONE low freq clock for 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
RF: C3 1p - L1 4.7nH - C4 1.2p - L5 2.2nH = Nordic config 7 match @ PS p952 fig 224 + p953 table 83 used on config 5's supply (POWER note): Nordic shows no such pair C3 ground -> VSS_PA ball, not the plane @ PS p968 C3 / C4 = +-0.1p parts, Nordic asks NP0 5% @ PS p953 L6 6.8nH = Walsin's match on t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
CLOCK START: Y1 runs whenever the board has power, firmware can NOT switch it valid within 1s at 25C, 3s over -40..105C @ TCXO DS p5, the MCU runs long before -> firmware MUST boot on LFRC, then stop LFCLK, select the TCXO, restart (README F4) LFCLKSRC must NOT be written while LFCLK runs @ PS p160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
BUSES: the speeds are MAX values for firmware (README F6) card SPI = SPIM3 at 16MHz: default speed ends at 25MHz @ SD spec p253, SPIM steps 8 / 16 / 32 @ PS p734 IMU SPI = SPIM2 at 4MHz: MCU data valid up to 59ns after the edge @ PS p739, IMU needs 13ns @ ICM DS p24 I2C A (charger + gauge) = TWIM0,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
MCU PINS (HIGH = 3.0V VDD, LOW = GND) P0.00 XL1 (D2) In 32.768kHz clock in from TCXO via R1 100R, XL2 open. boot on LFRC first (README F4) P0.04 BTN (J1) In start / stop button HIGH = pressed. NO resistor: internal PULLDOWN + SENSE high = wake (README F6) P0.05 MAG_INT (K2) In magnetometer measurem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
USB: D+/D- straight to the MCU, external pullup forbidden @ PS p853, full speed 12Mbps @ PS p850 R5 2.2R in the VBUS feed = Nordic's optional series R, "recommended for new designs" @ PS p938 source + cable + R5 must stay <= 6R @ PS p157 C21 4.7u on VBUS, C20 4.7u on DECUSB (>= 2.35u @ PS p157)

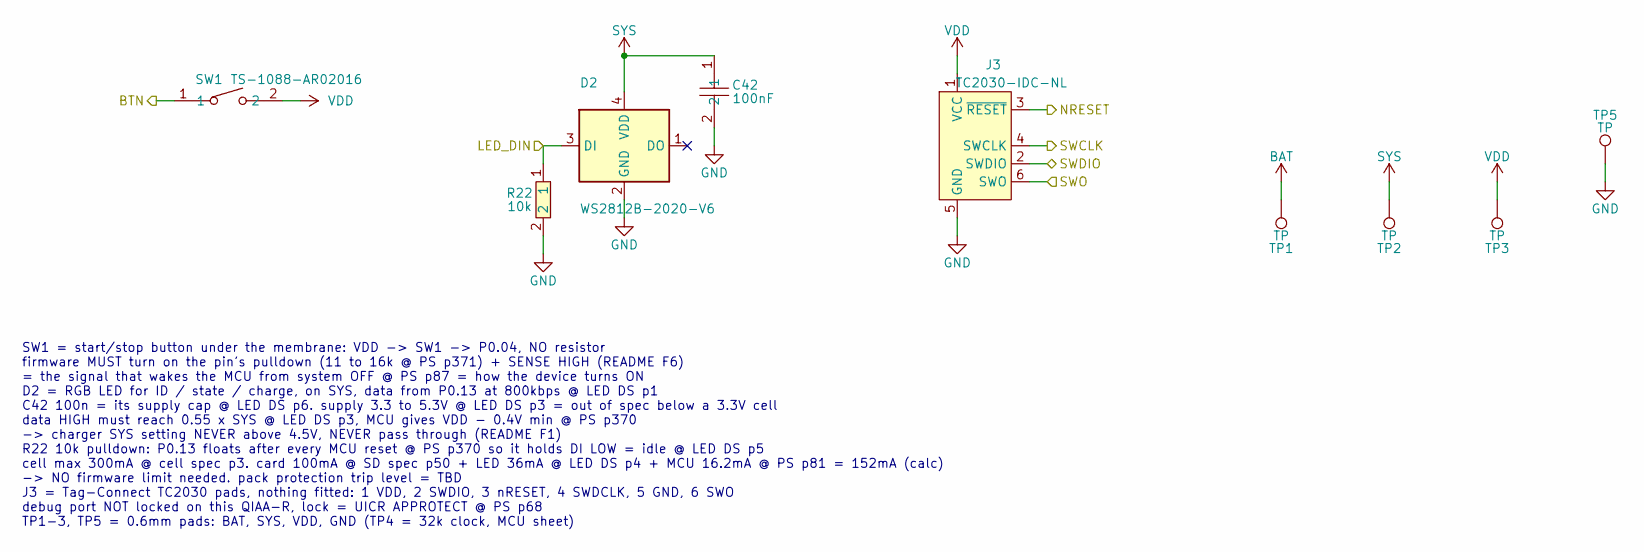
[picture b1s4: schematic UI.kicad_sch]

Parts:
C42: 100nF; CAP_100nF_16V_X7R_0402_CL05B104KO5NNNC; Tolerance +-10%; Voltage 16V; MPN CL05B104KO5NNNC; LCSC Part # C1525
D2: WS2812B-2020-V6; LED_WS2812B-2020-V6; MPN WS2812B-2020-V6; LCSC Part # C52917434
J3: TC2030-IDC-NL; CONN_SWD_TC2030-NL; MPN TC2030-IDC-NL
R22: 10k; RES_10k_0402_0402WGF1002TCE; Tolerance +-1%; MPN 0402WGF1002TCE; LCSC Part # C25744
SW1: TS-1088-AR02016; SW_TS-1088-AR02016; MPN TS-1088-AR02016; LCSC Part # C720477
TP1, TP2, TP3, TP5: TP; TP_0p6mm

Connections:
/MCU/BTN: SW1.1; also elsewhere on the board
/MCU/LED_DIN: D2.3 (DI), R22.1; also elsewhere on the board
/MCU/NRESET: J3.3 (~RESET); also elsewhere on the board
/MCU/SWCLK: J3.4 (SWCLK); also elsewhere on the board
/MCU/SWDIO: J3.2 (SWDIO); also elsewhere on the board
/MCU/SWO: J3.6 (SWO); also elsewhere on the board
BAT: TP1.1 (1_1); also elsewhere on the board
GND: C42.2, D2.2 (GND), J3.5 (GND), R22.2, TP5.1 (1_1); also elsewhere on the board
SYS: C42.1, D2.4 (VDD), TP2.1 (1_1); also elsewhere on the board
VDD: J3.1 (VCC), SW1.2, TP3.1 (1_1); also elsewhere on the board

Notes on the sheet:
SW1 = start/stop button under the membrane: VDD -> SW1 -> P0.04, NO resistor firmware MUST turn on the pin's pulldown (11 to 16k @ PS p371) + SENSE HIGH (README F6) = the signal that wakes the MCU from system OFF @ PS p87 = how the device turns ON D2 = RGB LED for ID / state / charge, on SYS, data 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

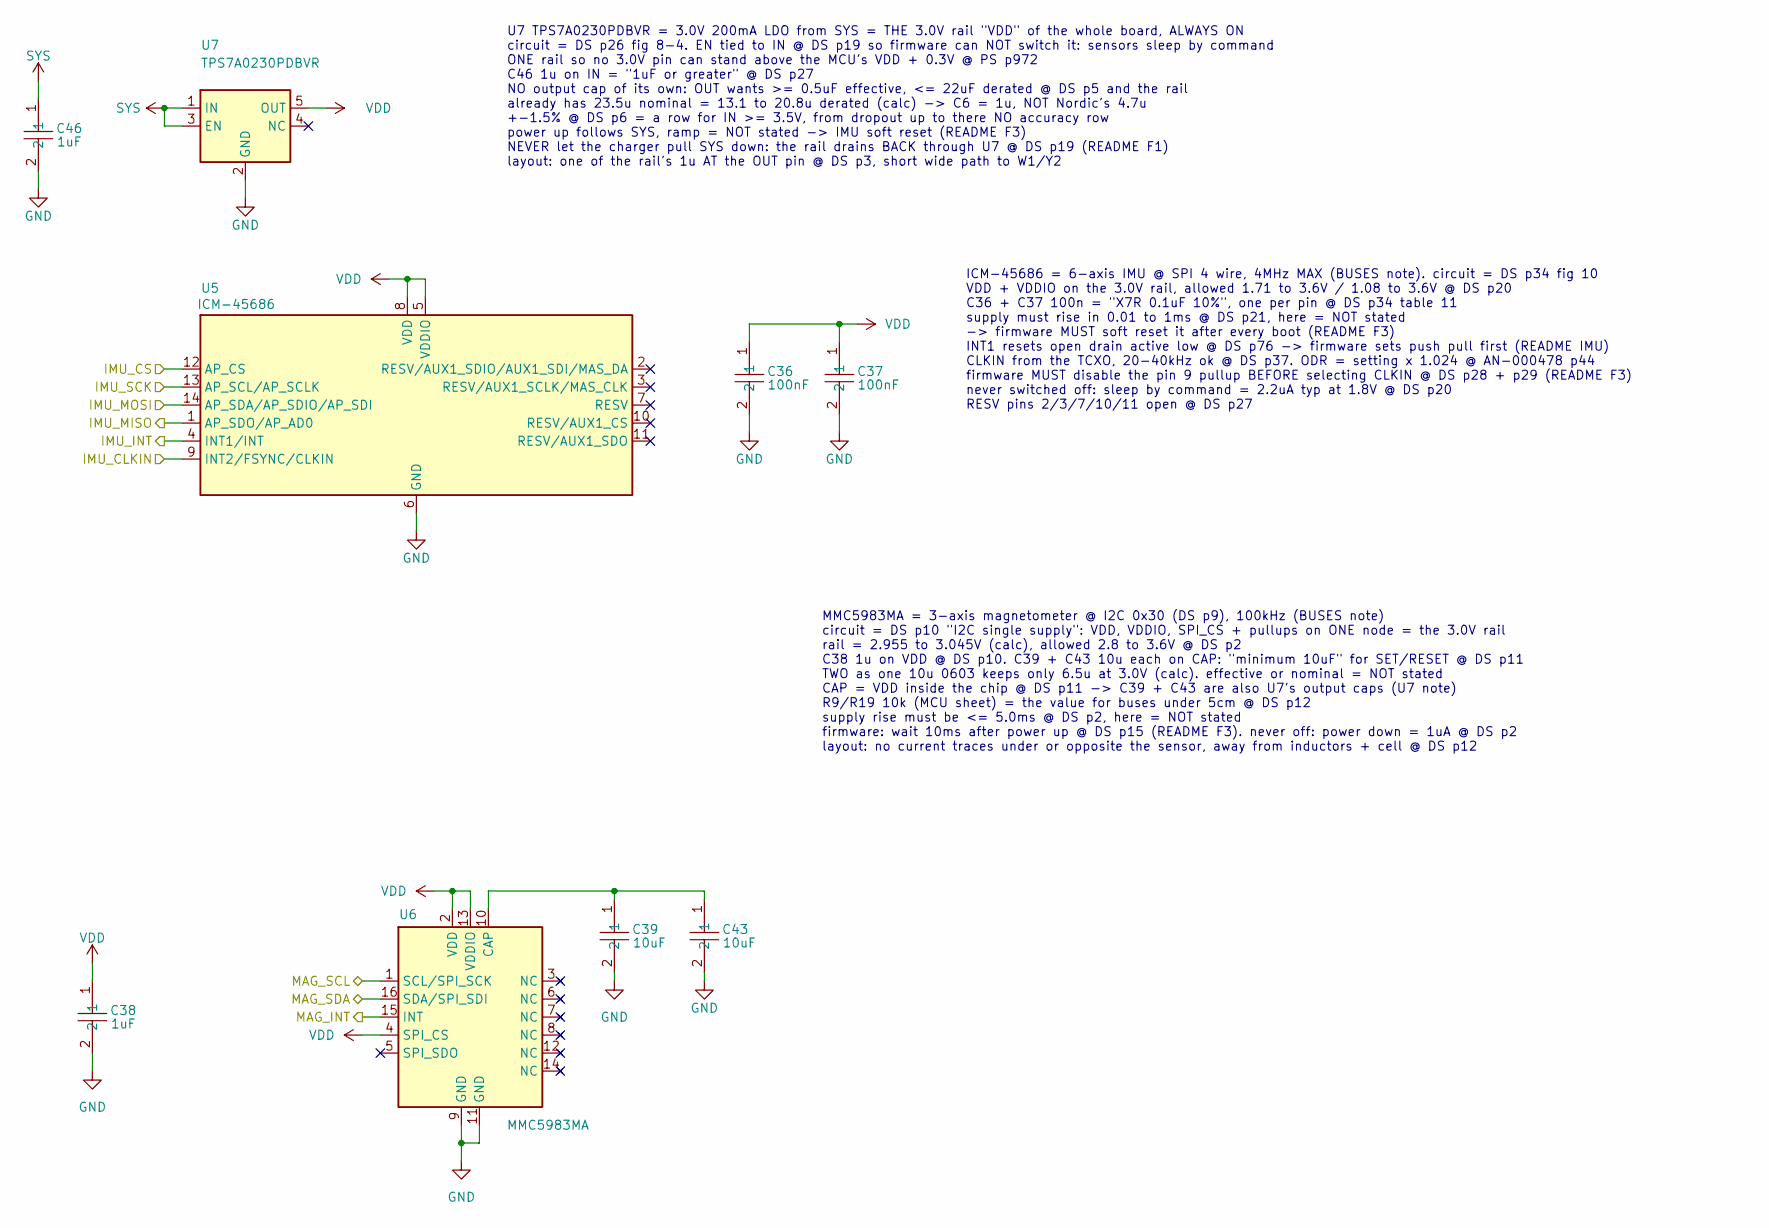
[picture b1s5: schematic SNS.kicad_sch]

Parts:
C36, C37: 100nF; CAP_100nF_16V_X7R_0402_CL05B104KO5NNNC; Tolerance +-10%; Voltage 16V; MPN CL05B104KO5NNNC; LCSC Part # C1525
C38, C46: 1uF; CAP_1uF_25V_X5R_0402_CL05A105KA5NQNC; Tolerance +-10%; Voltage 25V; MPN CL05A105KA5NQNC; LCSC Part # C52923
C39, C43: 10uF; CAP_10uF_25V_X5R_0603_CL10A106MA8NRNC; Tolerance +-20%; Voltage 25V; MPN CL10A106MA8NRNC; LCSC Part # C96446
U5: ICM-45686; IMU_ICM-45686; MPN ICM-45686; LCSC Part # C22459454
U6: MMC5983MA; MAG_MMC5983MA; MPN MMC5983MA; LCSC Part # C404329
U7: TPS7A0230PDBVR; LDO_3V0_TPS7A0230PDBVR; MPN TPS7A0230PDBVR; LCSC Part # C3747031

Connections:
/MCU/CLK32K_IMU: U5.9 (INT2/FSYNC/CLKIN); also elsewhere on the board
/MCU/IMU_CS: U5.12 (AP_CS); also elsewhere on the board
/MCU/IMU_INT: U5.4 (INT1/INT); also elsewhere on the board
/MCU/IMU_MISO: U5.1 (AP_SDO/AP_AD0); also elsewhere on the board
/MCU/IMU_MOSI: U5.14 (AP_SDA/AP_SDIO/AP_SDI); also elsewhere on the board
/MCU/IMU_SCK: U5.13 (AP_SCL/AP_SCLK); also elsewhere on the board
/MCU/MAG_INT: U6.15 (INT); also elsewhere on the board
/MCU/MAG_SCL: U6.1 (SCL/SPI_SCK); also elsewhere on the board
/MCU/MAG_SDA: U6.16 (SDA/SPI_SDI); also elsewhere on the board
GND: C36.2, C37.2, C38.2, C39.2, C43.2, C46.2, U5.6 (GND), U6.9 (GND), U6.11 (GND), U7.2 (GND); also elsewhere on the board
unnamed: C39.1, C43.1, U6.10 (CAP)
SYS: C46.1, U7.1 (IN), U7.3 (EN); also elsewhere on the board
VDD: C36.1, C37.1, C38.1, U5.5 (VDDIO), U5.8 (VDD), U6.2 (VDD), U6.4 (SPI_CS), U6.13 (VDDIO), U7.5 (OUT); also elsewhere on the board

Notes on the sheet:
U7 TPS7A0230PDBVR = 3.0V 200mA LDO from SYS = THE 3.0V rail "VDD" of the whole board, ALWAYS ON circuit = DS p26 fig 8-4. EN tied to IN @ DS p19 so firmware can NOT switch it: sensors sleep by command ONE rail so no 3.0V pin can stand above the MCU's VDD + 0.3V @ PS p972 C46 1u on IN = "1uF or grea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
ICM-45686 = 6-axis IMU @ SPI 4 wire, 4MHz MAX (BUSES note). circuit = DS p34 fig 10 VDD + VDDIO on the 3.0V rail, allowed 1.71 to 3.6V / 1.08 to 3.6V @ DS p20 C36 + C37 100n = "X7R 0.1uF 10%", one per pin @ DS p34 table 11 supply must rise in 0.01 to 1ms @ DS p21, here = NOT stated -> firmware MUST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
MMC5983MA = 3-axis magnetometer @ I2C 0x30 (DS p9), 100kHz (BUSES note) circuit = DS p10 "I2C single supply": VDD, VDDIO, SPI_CS + pullups on ONE node = the 3.0V rail rail = 2.955 to 3.045V (calc), allowed 2.8 to 3.6V @ DS p2 C38 1u on VDD @ DS p10. C39 + C43 10u each on CAP: "minimum 10uF" for SET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

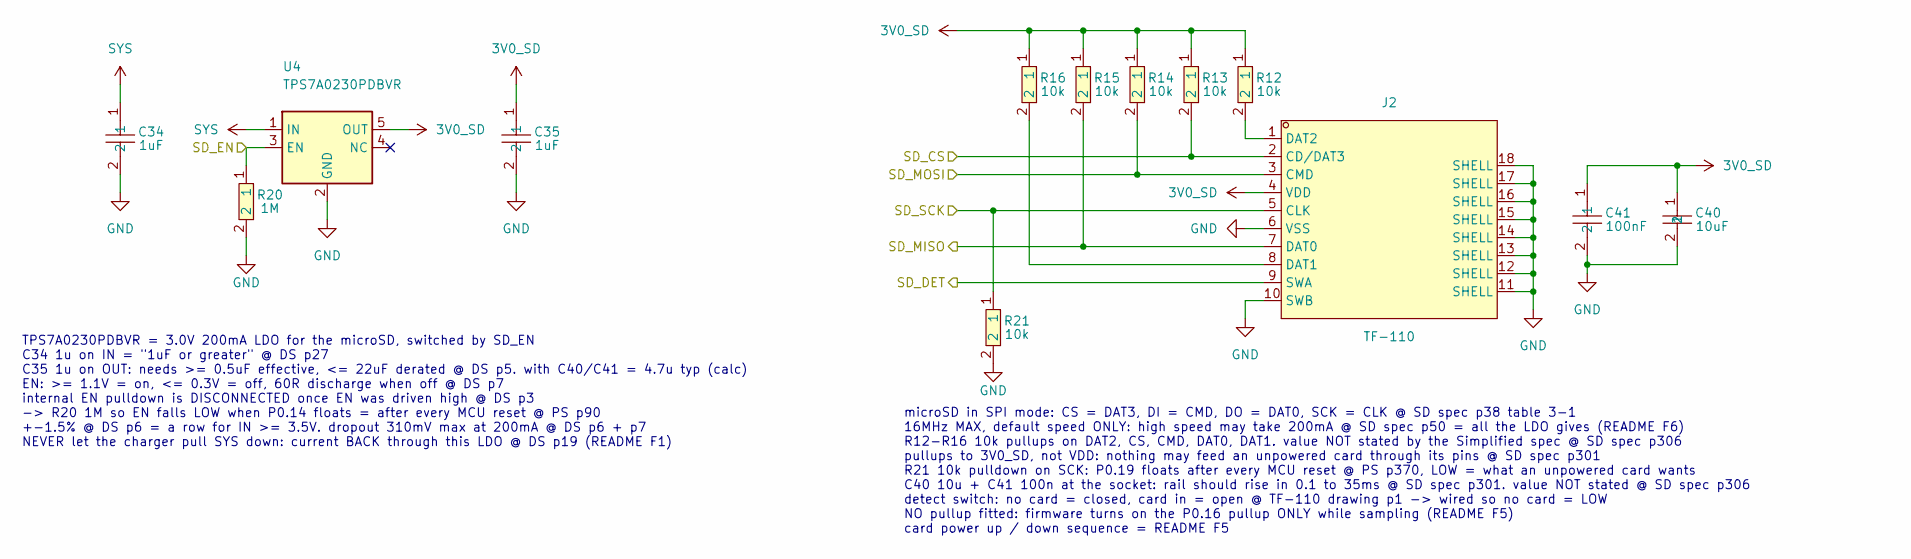
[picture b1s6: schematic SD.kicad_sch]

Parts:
C34, C35: 1uF; CAP_1uF_25V_X5R_0402_CL05A105KA5NQNC; Tolerance +-10%; Voltage 25V; MPN CL05A105KA5NQNC; LCSC Part # C52923
C40: 10uF; CAP_10uF_6V3_X5R_0402_CL05A106MQ5NUNC; Tolerance +-20%; Voltage 6.3V; MPN CL05A106MQ5NUNC; LCSC Part # C15525
C41: 100nF; CAP_100nF_16V_X7R_0402_CL05B104KO5NNNC; Tolerance +-10%; Voltage 16V; MPN CL05B104KO5NNNC; LCSC Part # C1525
J2: TF-110; CONN_MICROSD_TF-110; MPN TF-110; LCSC Part # C266613
R12, R13, R14, R15, R16, R21: 10k; RES_10k_0402_0402WGF1002TCE; Tolerance +-1%; MPN 0402WGF1002TCE; LCSC Part # C25744
R20: 1M; RES_1M_0402_0402WGF1004TCE; Tolerance +-1%; MPN 0402WGF1004TCE; LCSC Part # C26083
U4: TPS7A0230PDBVR; LDO_3V0_TPS7A0230PDBVR; MPN TPS7A0230PDBVR; LCSC Part # C3747031

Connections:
3V0_SD: C35.1, C40.1, C41.1, J2.4 (VDD), R12.1, R13.1, R14.1, R15.1, R16.1, U4.5 (OUT)
/MCU/SD_CS: J2.2 (CD/DAT3), R13.2; also elsewhere on the board
/MCU/SD_DET: J2.9 (SWA); also elsewhere on the board
/MCU/SD_EN: R20.1, U4.3 (EN); also elsewhere on the board
/MCU/SD_MISO: J2.7 (DAT0), R15.2; also elsewhere on the board
/MCU/SD_MOSI: J2.3 (CMD), R14.2; also elsewhere on the board
/MCU/SD_SCK: J2.5 (CLK), R21.1; also elsewhere on the board
GND: C34.2, C35.2, C40.2, C41.2, J2.6 (VSS), J2.10 (SWB), J2.11 (SHELL), J2.12 (SHELL), J2.13 (SHELL), J2.14 (SHELL), J2.15 (SHELL), J2.16 (SHELL), J2.17 (SHELL), J2.18 (SHELL), R20.2, R21.2, U4.2 (GND); also elsewhere on the board
unnamed: J2.8 (DAT1), R16.2
unnamed: J2.1 (DAT2), R12.2
SYS: C34.1, U4.1 (IN); also elsewhere on the board

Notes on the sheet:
TPS7A0230PDBVR = 3.0V 200mA LDO for the microSD, switched by SD_EN C34 1u on IN = "1uF or greater" @ DS p27 C35 1u on OUT: needs >= 0.5uF effective, <= 22uF derated @ DS p5. with C40/C41 = 4.7u typ (calc) EN: >= 1.1V = on, <= 0.3V = off, 60R discharge when off @ DS p7 internal EN pulldown is DISCON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
microSD in SPI mode: CS = DAT3, DI = CMD, DO = DAT0, SCK = CLK @ SD spec p38 table 3-1 16MHz MAX, default speed ONLY: high speed may take 200mA @ SD spec p50 = all the LDO gives (README F6) R12-R16 10k pullups on DAT2, CS, CMD, DAT0, DAT1. value NOT stated by the Simplified spec @ SD spec p306 pull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
